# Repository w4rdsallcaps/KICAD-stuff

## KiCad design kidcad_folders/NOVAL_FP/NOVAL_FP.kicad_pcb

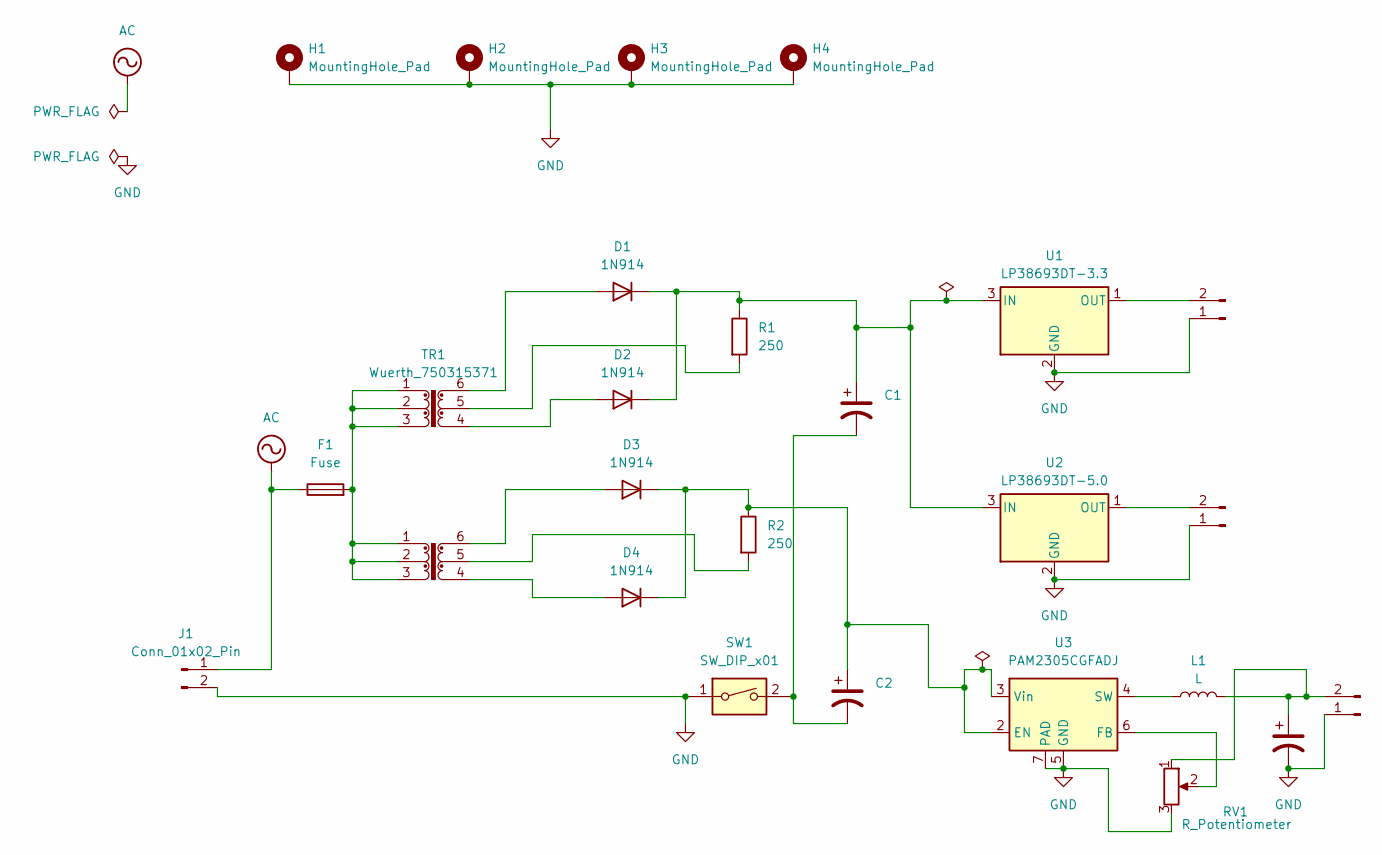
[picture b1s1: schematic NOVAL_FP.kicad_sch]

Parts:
C1, C2, C3: C_Polarized_US; CP_Axial_L10.0mm_D4.5mm_P15.00mm_Horizontal
D1, D2, D3, D4: 1N914; D_DO-35_SOD27_P7.62mm_Horizontal
F1: Fuse; L_TechFuse_SL0420
H1, H2, H3, H4: MountingHole_Pad; MountingHole_2.2mm_M2_DIN965_Pad
J1, J2, J3, J4: Conn_01x02_Pin; PhoenixContact_MSTBA_2,5_2-G-5,08_1x02_P5.08mm_Horizontal
L1: L; L_Wurth_WE-LQSH-2010
R1, R2: 250; R_Axial_DIN0204_L3.6mm_D1.6mm_P7.62mm_Horizontal
RV1: R_Potentiometer; Potentiometer_Bourns_3266Y_Vertical
SW1: SW_DIP_x01; SW_DIP_SPSTx01_Slide_6.7x4.1mm_W8.61mm_P2.54mm_LowProfile
TR1, TR2: Wuerth_750315371; Transformer_Wuerth_750315371
U1: LP38693DT-3.3; TO-252-2
U2: LP38693DT-5.0; TO-252-2
U3: PAM2305CGFADJ; DFN-6-1EP_2x2mm_P0.65mm_EP1x1.6mm

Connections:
AC: F1.1, J1.1
GND: C3.2, H1.1 (1_1), H2.1 (1_1), H3.1 (1_1), H4.1 (1_1), J1.2, J2.1, J3.1, J4.1, RV1.3, SW1.1, U1.2 (GND), U2.2 (GND), U3.5 (GND), U3.7 (PAD)
unnamed: C1.2, C2.2, SW1.2
unnamed: D1.2 (A), TR1.6
unnamed: C1.1, D1.1 (K), D2.1 (K), R1.1, U1.3 (IN), U2.3 (IN)
unnamed: D2.2 (A), TR1.4
unnamed: D3.2 (A), TR2.6
unnamed: C2.1, D3.1 (K), D4.1 (K), R2.1, U3.2 (EN), U3.3 (Vin)
unnamed: D4.2 (A), TR2.4
unnamed: F1.2, TR1.1, TR1.2, TR1.3, TR2.1, TR2.2, TR2.3
unnamed: C3.1, J2.2, L1.2, RV1.1
unnamed: J3.2, U2.1 (OUT)
unnamed: J4.2, U1.1 (OUT)
unnamed: R1.2, TR1.5
unnamed: R2.2, TR2.5
unnamed: RV1.2, U3.6 (FB)
unnamed: L1.1, U3.4 (SW)

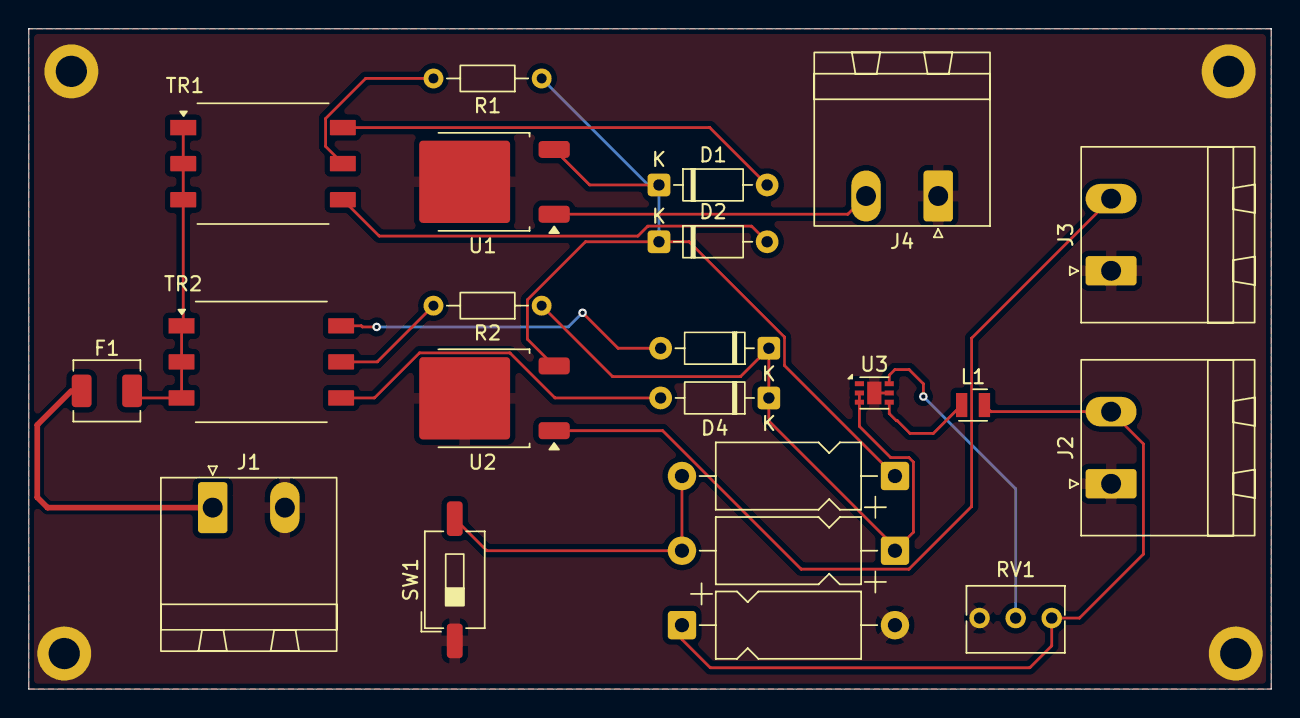
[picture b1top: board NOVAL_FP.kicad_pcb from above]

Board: 2 copper layers, 87.5 x 46.5 mm, 26 parts (0 on the bottom side), 17 nets.

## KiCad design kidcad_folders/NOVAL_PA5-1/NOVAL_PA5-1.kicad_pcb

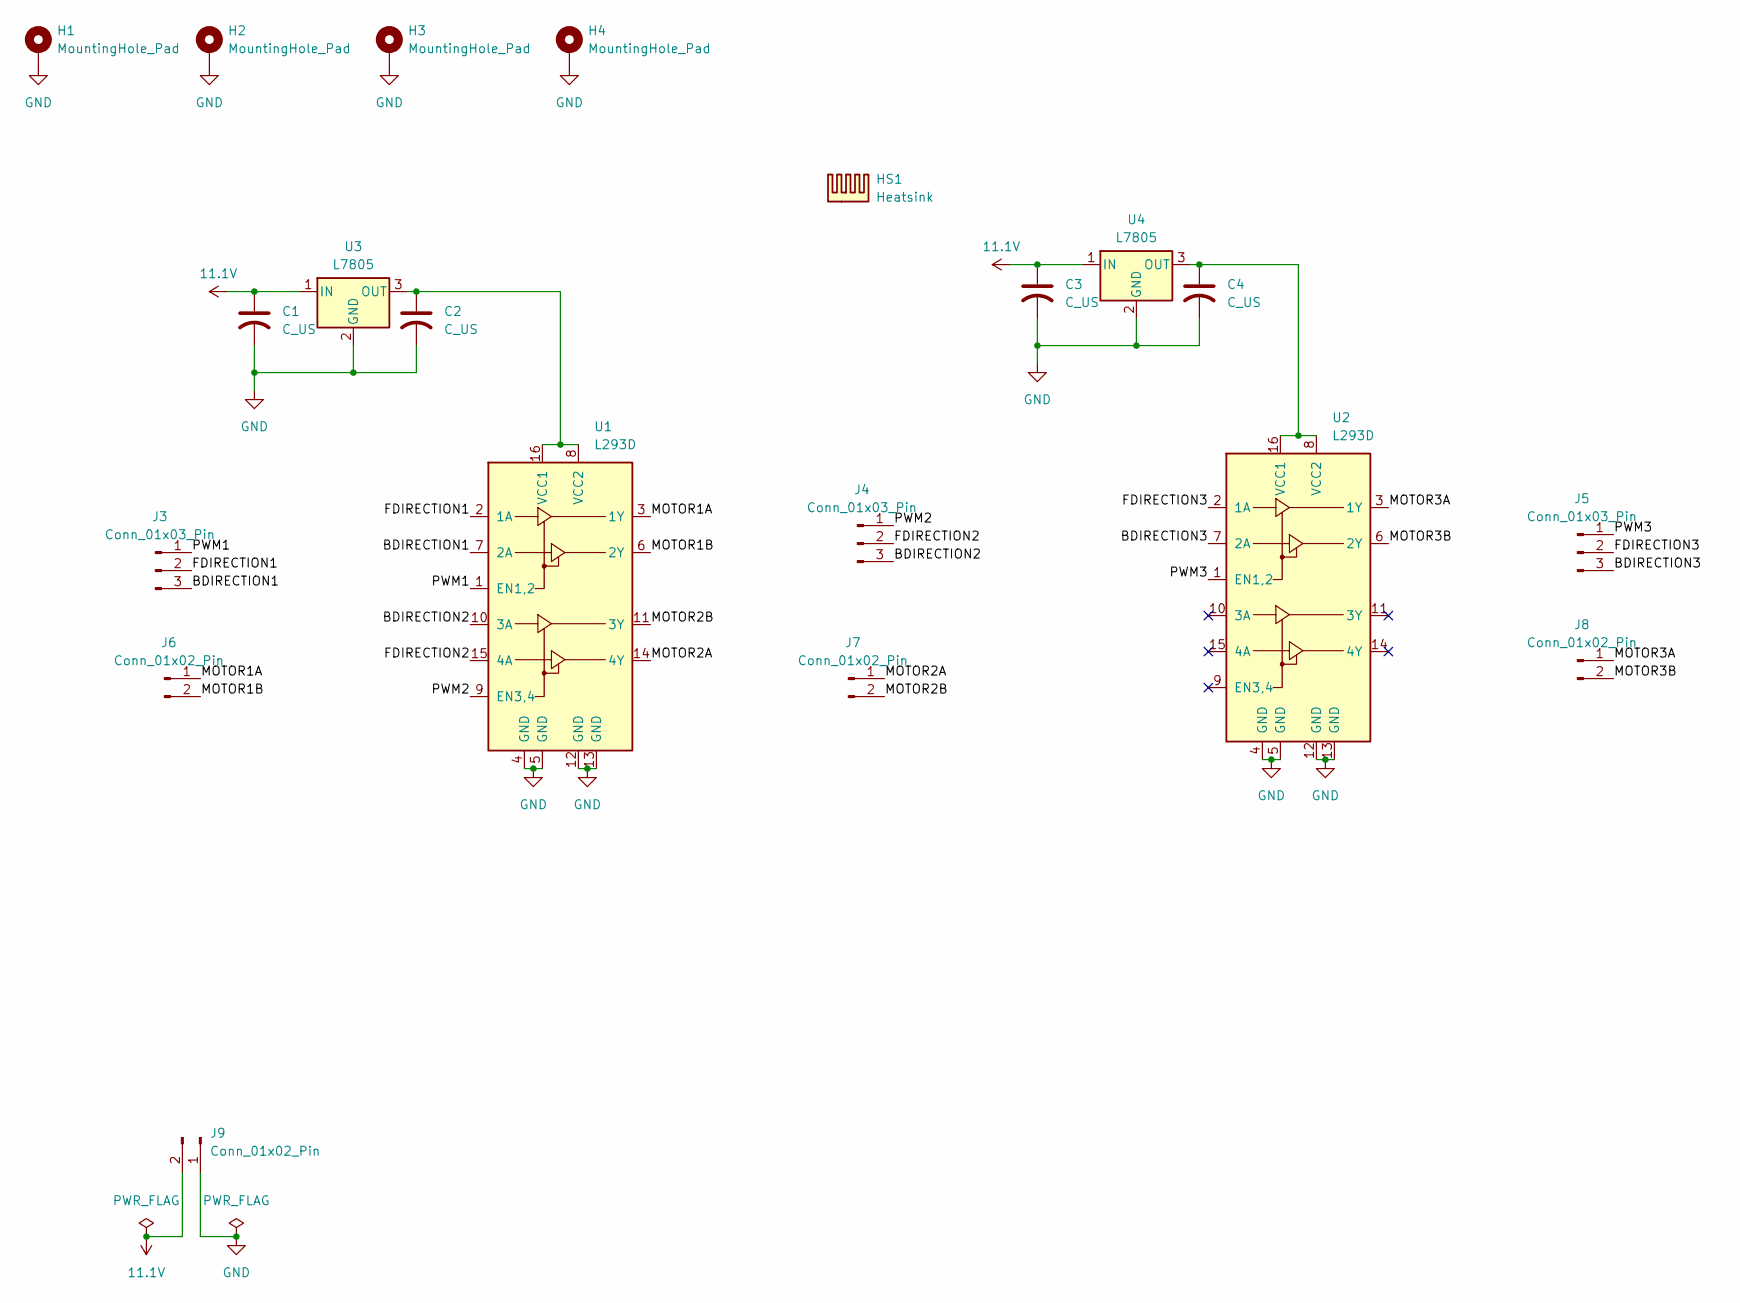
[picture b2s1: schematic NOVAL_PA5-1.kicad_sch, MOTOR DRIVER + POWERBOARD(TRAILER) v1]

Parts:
C1, C2, C3, C4: C_US; C_Axial_L5.1mm_D3.1mm_P10.00mm_Horizontal
H1, H2, H3, H4: MountingHole_Pad; MountingHole_2.2mm_M2_DIN965_Pad
HS1: Heatsink
J3, J4, J5: Conn_01x03_Pin; JST_PH_S3B-PH-K_1x03_P2.00mm_Horizontal
J6, J7, J8, J9: Conn_01x02_Pin; JST_EH_S2B-EH_1x02_P2.50mm_Horizontal
U1, U2: L293D; DIP-16_W7.62mm
U3, U4: L7805; TO-220-3_Vertical

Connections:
11.1V: C1.1, C3.1, J9.2, U3.1 (IN), U4.1 (IN)
/BDIRECTION1: J3.3, U1.7 (2A)
/BDIRECTION2: J4.3, U1.10 (3A)
/BDIRECTION3: J5.3, U2.7 (2A)
/FDIRECTION1: J3.2, U1.2 (1A)
/FDIRECTION2: J4.2, U1.15 (4A)
/FDIRECTION3: J5.2, U2.2 (1A)
/MOTOR1A: J6.1, U1.3 (1Y)
/MOTOR1B: J6.2, U1.6 (2Y)
/MOTOR2A: J7.1, U1.14 (4Y)
/MOTOR2B: J7.2, U1.11 (3Y)
/MOTOR3A: J8.1, U2.3 (1Y)
/MOTOR3B: J8.2, U2.6 (2Y)
/PWM1: J3.1, U1.1 (EN1,2)
/PWM2: J4.1, U1.9 (EN3,4)
/PWM3: J5.1, U2.1 (EN1,2)
GND: C1.2, C2.2, C3.2, C4.2, H1.1 (1_1), H2.1 (1_1), H3.1 (1_1), H4.1 (1_1), J9.1, U1.4 (GND), U1.5 (GND), U1.12 (GND), U1.13 (GND), U2.4 (GND), U2.5 (GND), U2.12 (GND), U2.13 (GND), U3.2 (GND), U4.2 (GND)
unnamed: C2.1, U1.8 (VCC2), U1.16 (VCC1), U3.3 (OUT)
unnamed: C4.1, U2.8 (VCC2), U2.16 (VCC1), U4.3 (OUT)

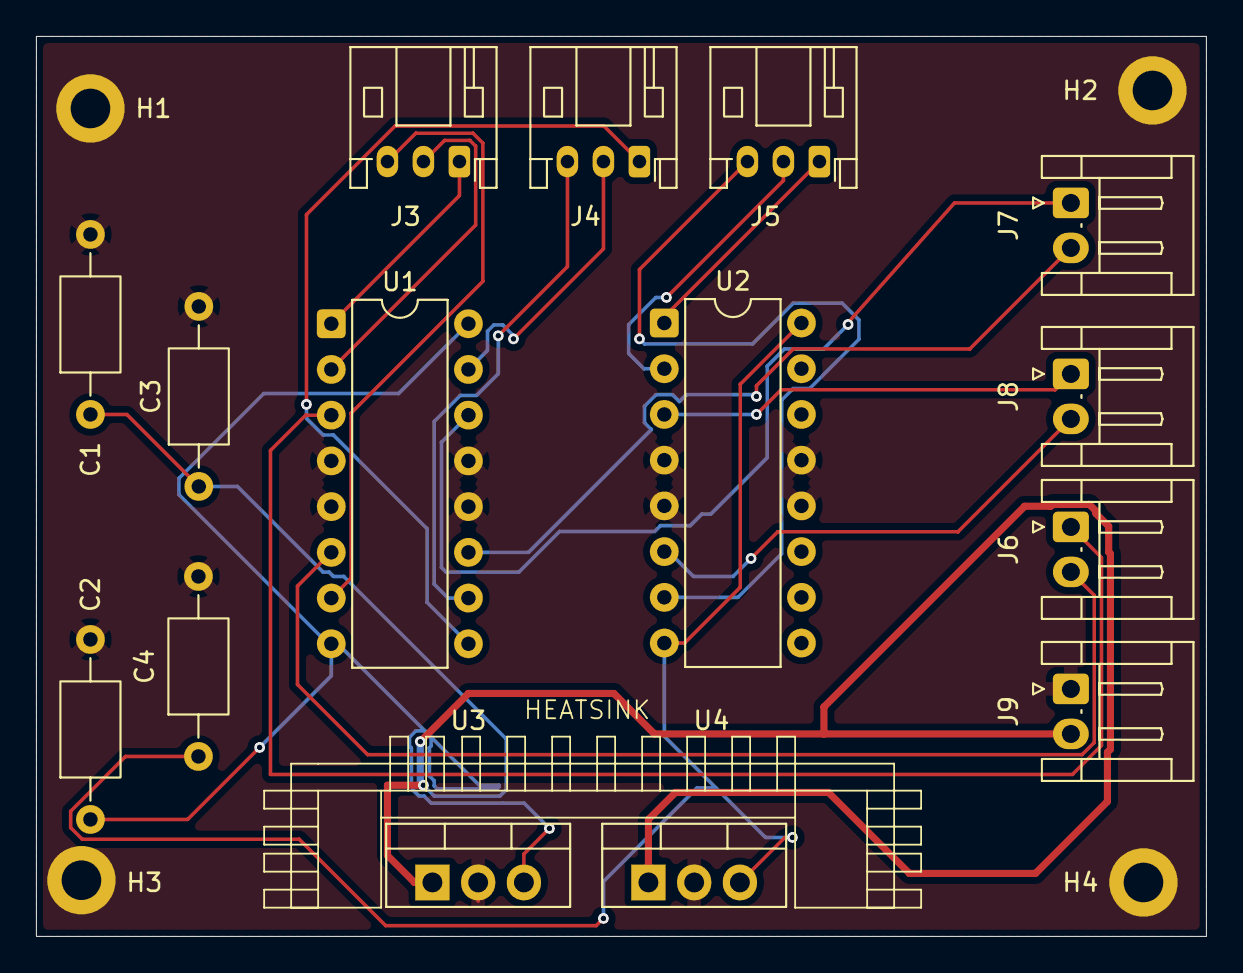
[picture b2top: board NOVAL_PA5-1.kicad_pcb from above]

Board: 2 copper layers, 65.0 x 50.0 mm, 19 parts (0 on the bottom side), 19 nets.

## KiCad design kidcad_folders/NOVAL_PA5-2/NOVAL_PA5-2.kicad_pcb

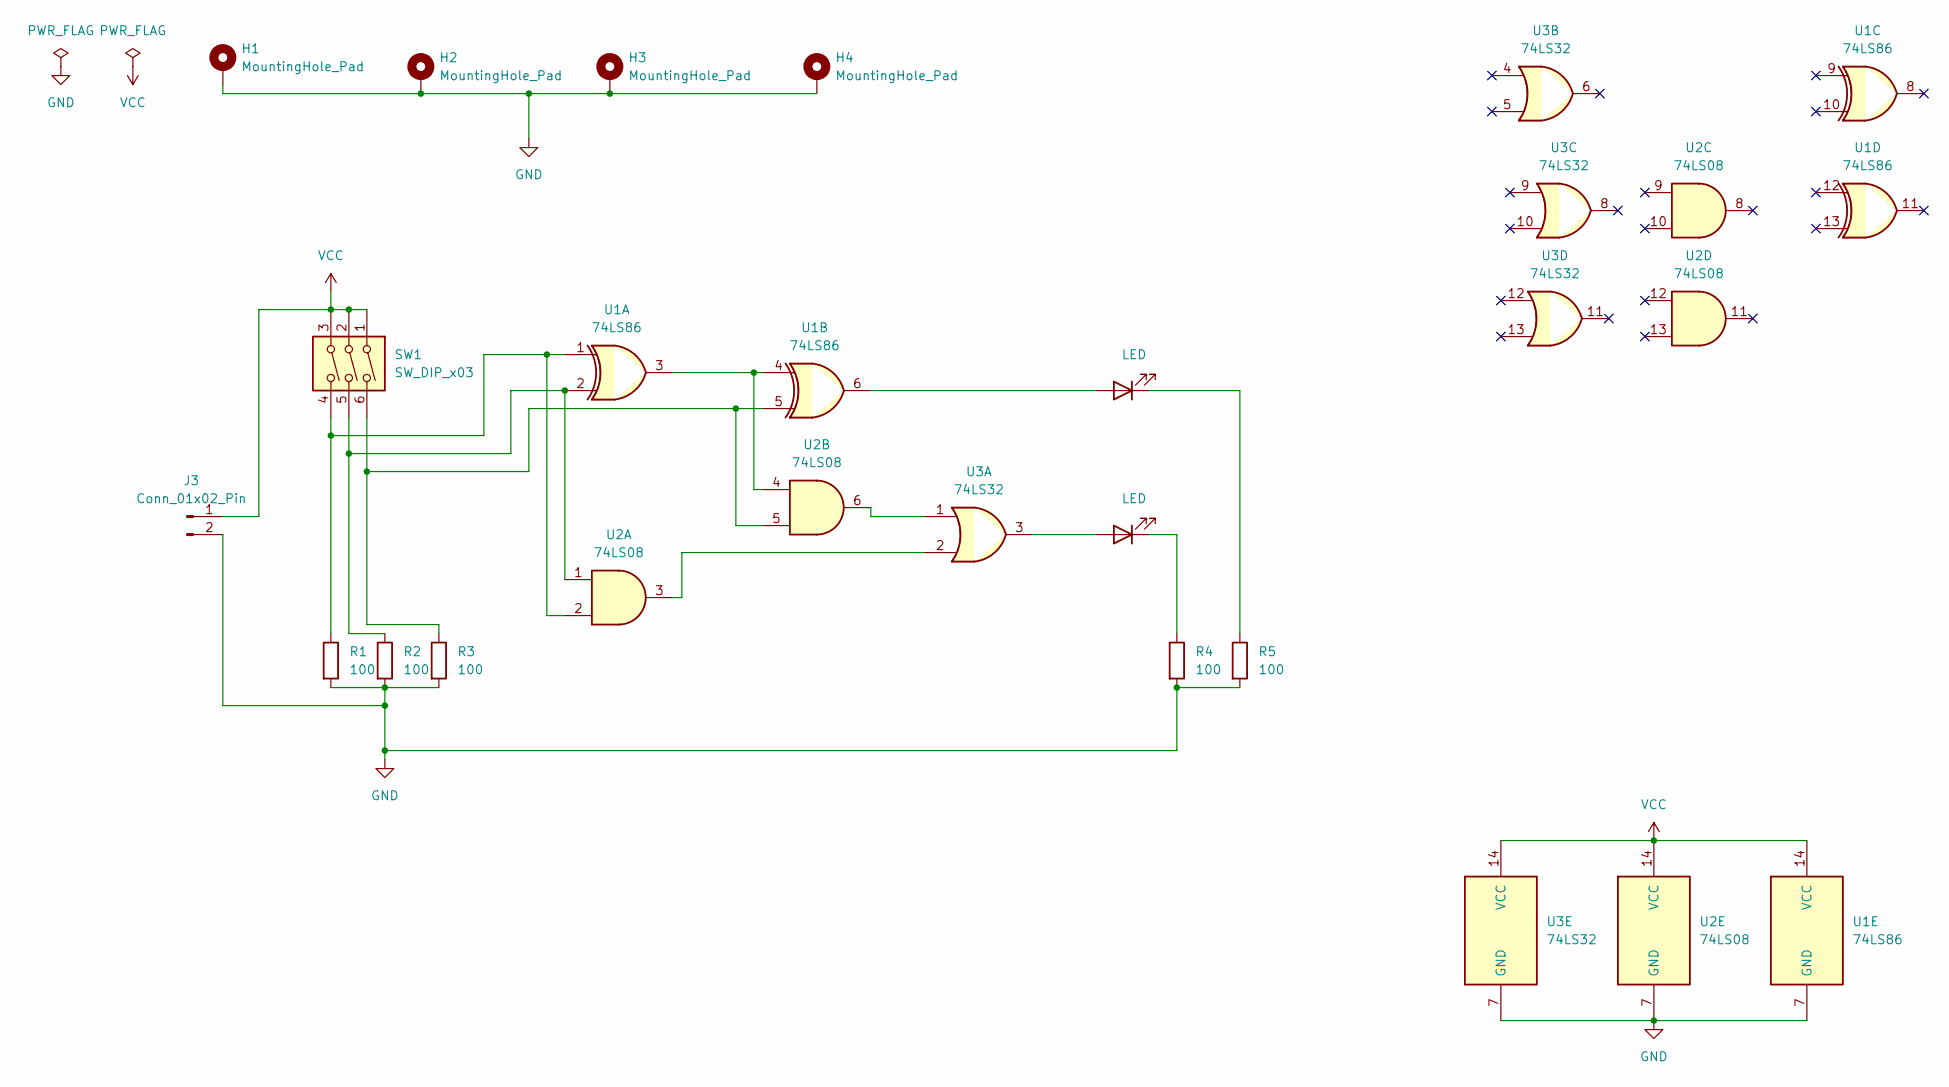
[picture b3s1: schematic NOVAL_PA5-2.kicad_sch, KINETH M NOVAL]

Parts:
H1, H2, H3, H4: MountingHole_Pad; MountingHole_2.2mm_M2_DIN965_Pad
J3: Conn_01x02_Pin; PinHeader_1x02_P2.00mm_Horizontal
L1, L2: LED; LED_D3.0mm
R1, R2, R3, R4, R5: 100; R_Axial_DIN0204_L3.6mm_D1.6mm_P5.08mm_Horizontal
SW1: SW_DIP_x03; MS12ANG03
U1: 74LS86; DIP-14_W7.62mm
U2: 74LS08; DIP-14_W7.62mm
U3: 74LS32; DIP-14_W7.62mm

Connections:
GND: H1.1 (1_1), H2.1 (1_1), H3.1 (1_1), H4.1 (1_1), J3.2, R1.2, R2.2, R3.2, R4.2, R5.2, U1.7 (GND), U2.7 (GND), U3.7 (GND)
unnamed: L1.2 (A), U1.6
unnamed: L1.1 (K), R5.1
unnamed: L2.2 (A), U3.3
unnamed: L2.1 (K), R4.1
unnamed: R1.1, SW1.4, U1.1, U2.2
unnamed: R2.1, SW1.5, U1.2, U2.1
unnamed: R3.1, SW1.6, U1.5, U2.5
unnamed: U1.3, U1.4, U2.4
unnamed: U2.3, U3.2
unnamed: U2.6, U3.1
VCC: J3.1, SW1.1, SW1.2, SW1.3, U1.14 (VCC), U2.14 (VCC), U3.14 (VCC)

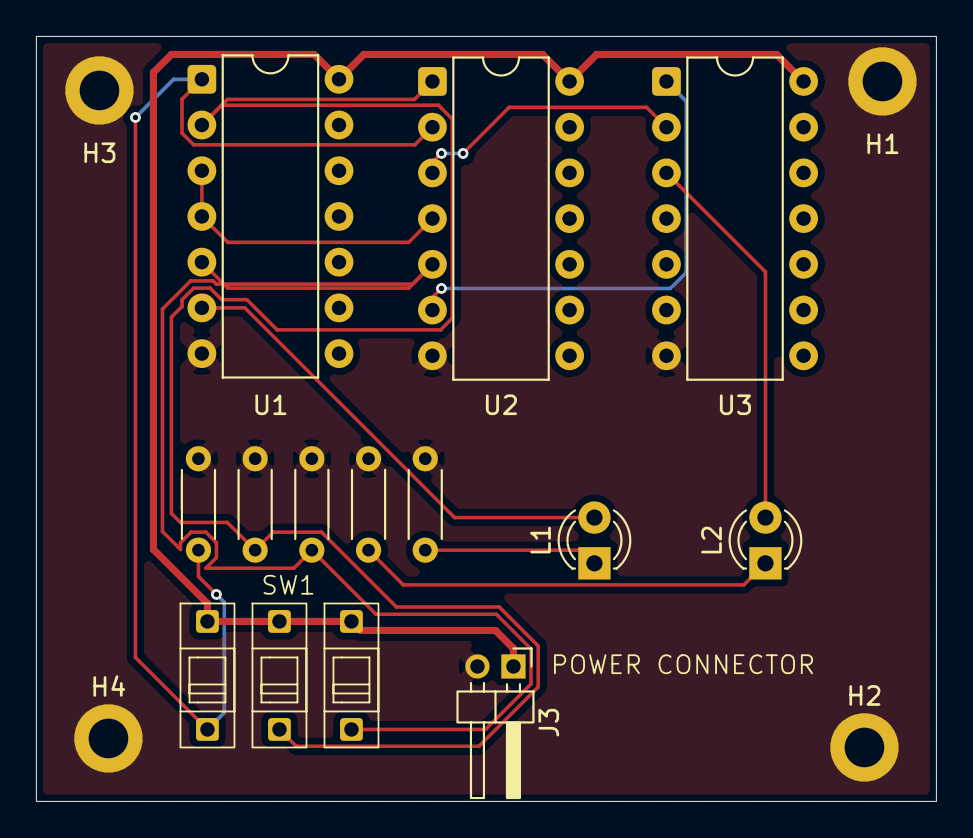
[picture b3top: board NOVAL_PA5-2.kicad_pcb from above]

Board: 2 copper layers, 50.0 x 42.5 mm, 16 parts (0 on the bottom side), 12 nets.

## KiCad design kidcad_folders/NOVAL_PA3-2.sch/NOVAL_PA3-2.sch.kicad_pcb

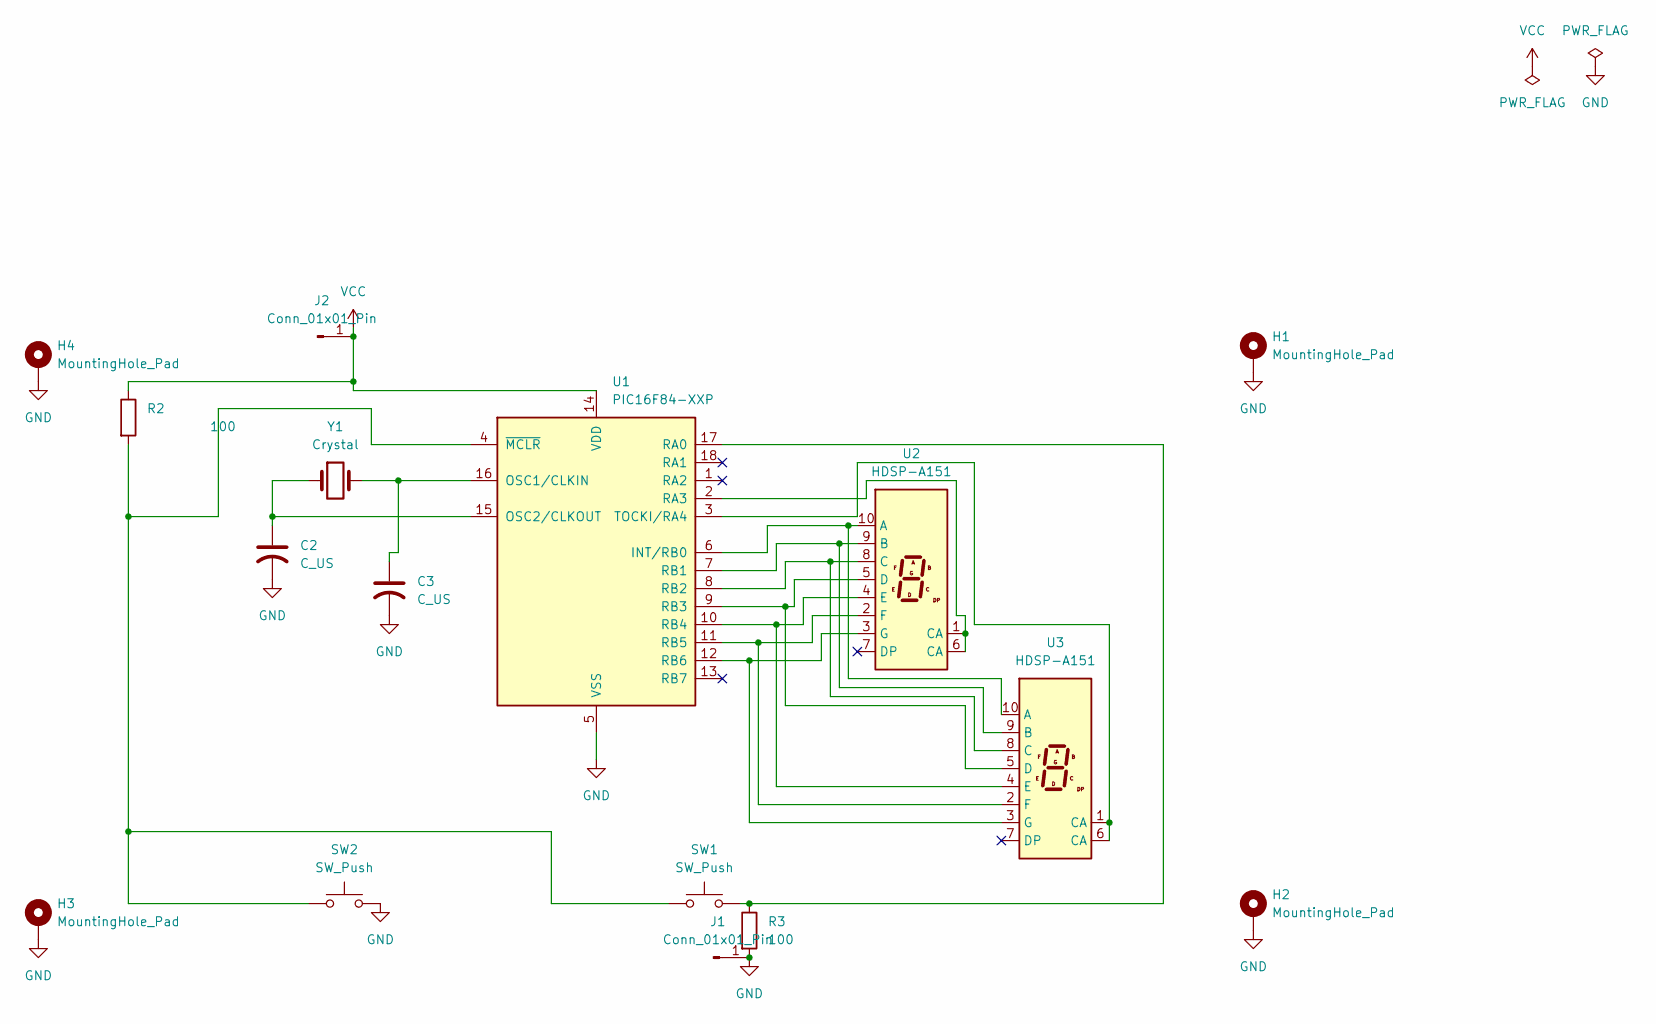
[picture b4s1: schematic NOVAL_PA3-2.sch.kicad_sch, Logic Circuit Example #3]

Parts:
C2, C3: C_US; CP_Axial_L10.0mm_D4.5mm_P15.00mm_Horizontal
H1, H2, H3, H4: MountingHole_Pad; MountingHole_3mm_Pad
J1, J2: Conn_01x01_Pin; SolderWire-0.127sqmm_1x01_D0.48mm_OD1mm
R2, R3: 100; R_Axial_DIN0204_L3.6mm_D1.6mm_P5.08mm_Horizontal
SW1, SW2: SW_Push; SW_PUSH_1P1T_6x3.5mm_H5.0_APEM_MJTP1250
U1: PIC16F84-XXP; DIP-18_W7.62mm
U2, U3: HDSP-A151
Y1: Crystal; Crystal_C38-LF_D3.0mm_L8.0mm_Vertical

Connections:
GND: C2.2, C3.2, H1.1 (1_1), H2.1 (1_1), H3.1 (1_1), H4.1 (1_1), J1.1 (Pin_1_1), R3.2, SW2.2, U1.5 (VSS)
unnamed: U1.6 (INT/RB0), U2.10 (A), U3.10 (A)
unnamed: C3.1, U1.16 (OSC1/CLKIN), Y1.2
unnamed: C2.1, U1.15 (OSC2/CLKOUT), Y1.1
unnamed: R3.1, SW1.2, U1.17 (RA0)
unnamed: U1.2 (RA3), U2.1 (CA), U2.6 (CA)
unnamed: U1.7 (RB1), U2.9 (B), U3.9 (B)
unnamed: U1.8 (RB2), U2.8 (C), U3.8 (C)
unnamed: U1.9 (RB3), U2.5 (D), U3.5 (D)
unnamed: U1.10 (RB4), U2.4 (E), U3.4 (E)
unnamed: U1.11 (RB5), U2.2 (F), U3.2 (F)
unnamed: U1.12 (RB6), U2.3 (G), U3.3 (G)
unnamed: U1.3 (TOCKI/RA4), U3.1 (CA), U3.6 (CA)
unnamed: R2.2, SW1.1, SW2.1, U1.4 (~MCLR)
VCC: J2.1 (Pin_1_1), R2.1, U1.14 (VDD)

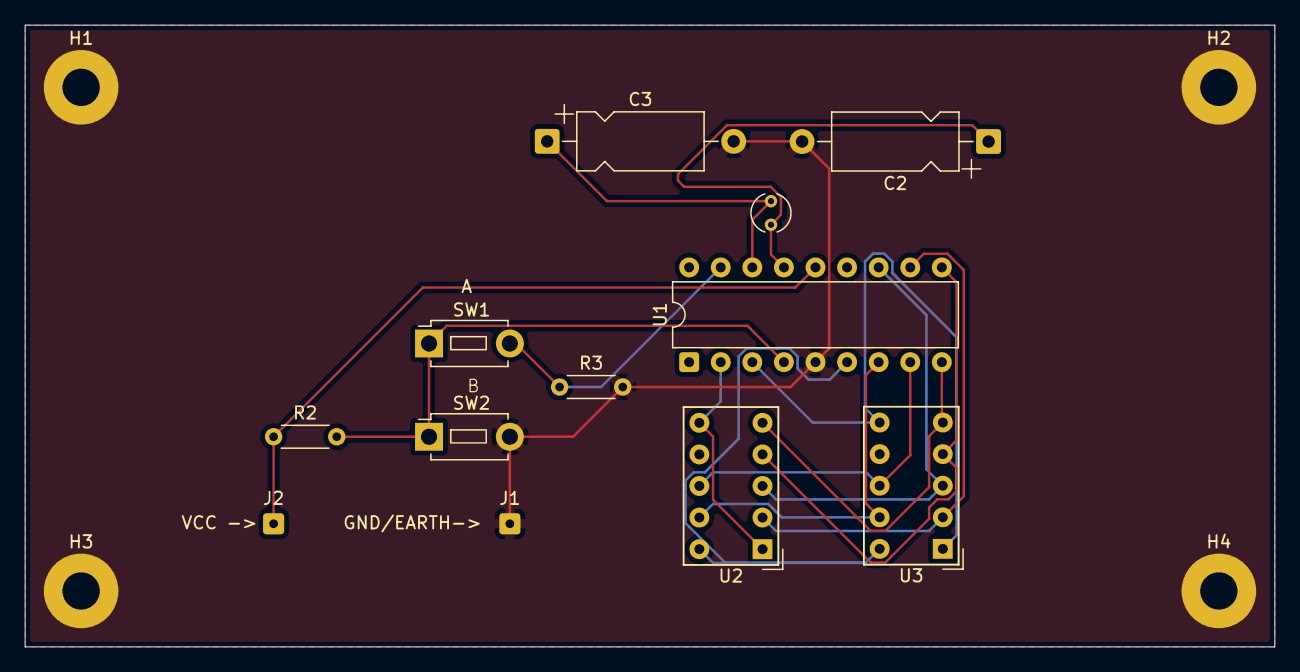
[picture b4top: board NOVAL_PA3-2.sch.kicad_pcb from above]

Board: 2 copper layers, 100.5 x 50.0 mm, 16 parts (0 on the bottom side), 15 nets.

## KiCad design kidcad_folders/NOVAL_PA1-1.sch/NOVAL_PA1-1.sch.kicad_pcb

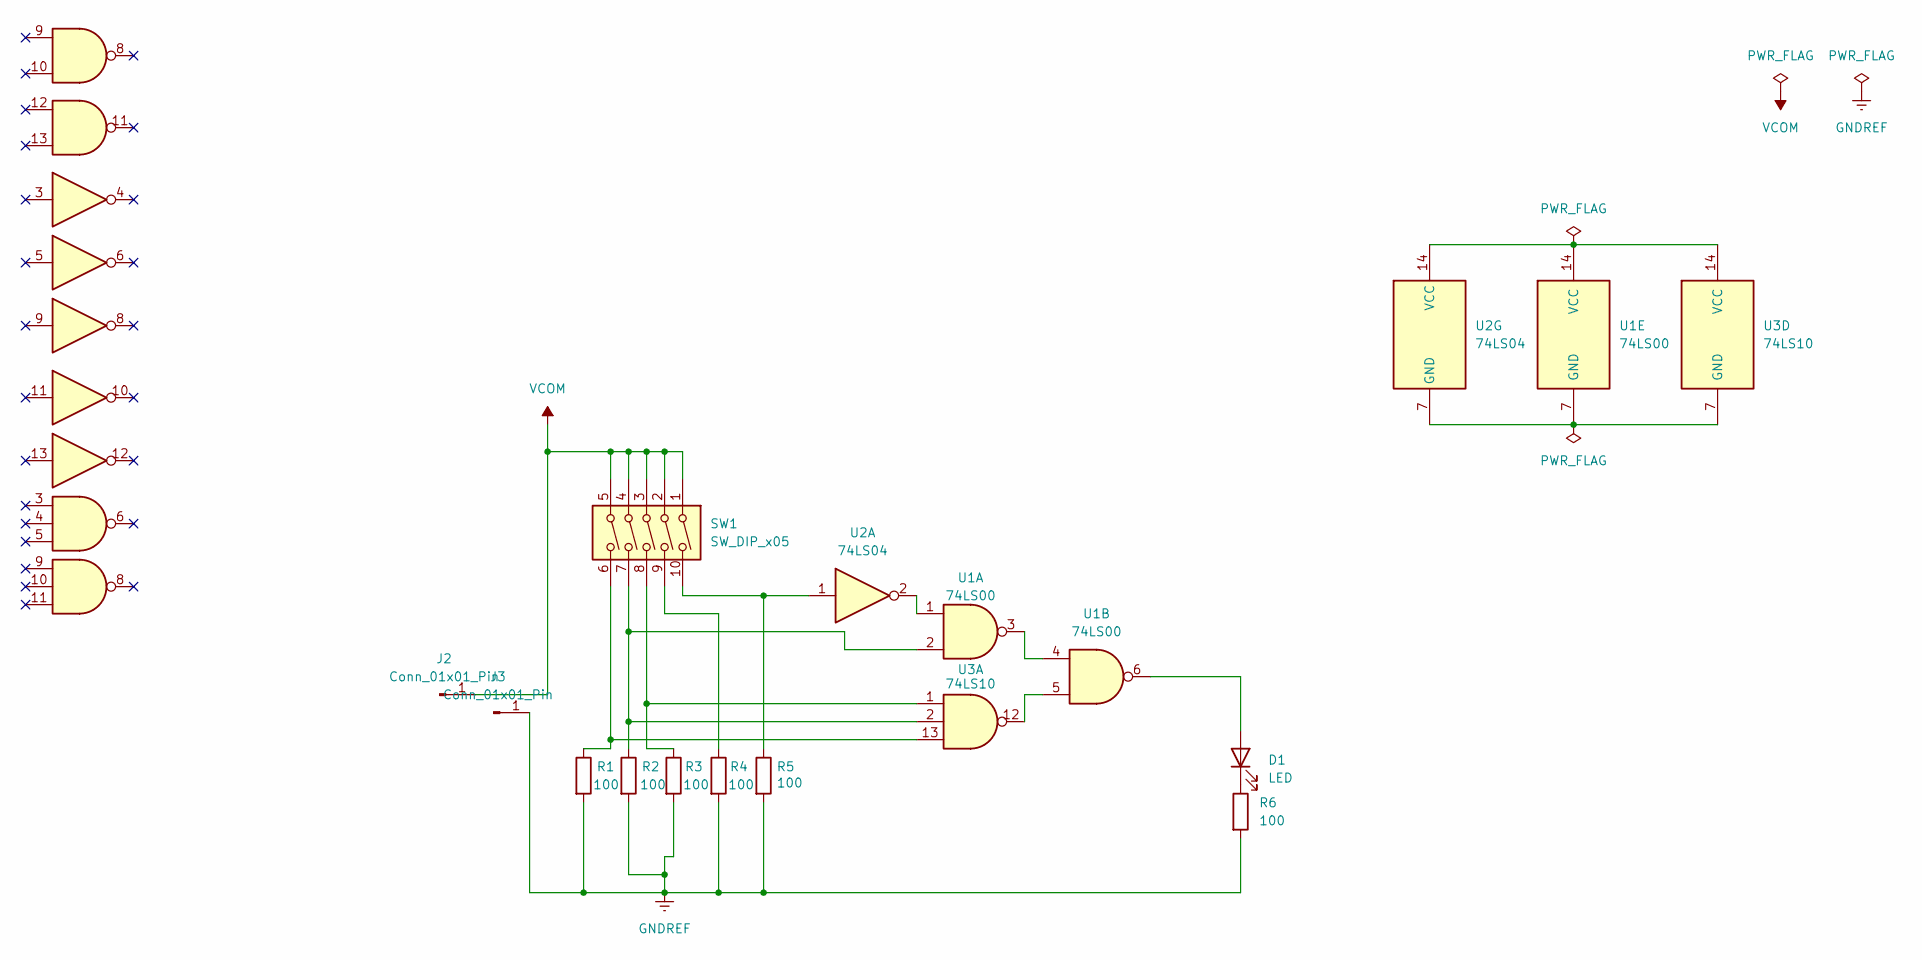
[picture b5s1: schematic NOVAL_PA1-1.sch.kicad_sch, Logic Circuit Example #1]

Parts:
D1: LED; LED_D3.0mm_Clear
J2, J3: Conn_01x01_Pin; SolderWire-1.5sqmm_1x01_D1.7mm_OD3.9mm
R1, R2, R3, R4, R5, R6: 100; R_Axial_DIN0207_L6.3mm_D2.5mm_P7.62mm_Horizontal
SW1: SW_DIP_x05; SW_DIP_SPSTx05_Slide_9.78x14.88mm_W7.62mm_P2.54mm
U1: 74LS00; DIP-14_W10.16mm
U2: 74LS04; DIP-14_W10.16mm
U3: 74LS10; DIP-14_W10.16mm

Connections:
GNDREF: J3.1 (Pin_1_1), R1.2, R2.2, R3.2, R4.2, R5.2, R6.2
unnamed: D1.2 (A), U1.6
unnamed: D1.1 (K), R6.1
unnamed: R1.1, SW1.6, U3.13
unnamed: R2.1, SW1.7, U1.2, U3.2
unnamed: R3.1, SW1.8, U3.1
unnamed: R4.1, SW1.9
unnamed: R5.1, SW1.10, U2.1
unnamed: U1.1, U2.2
unnamed: U1.3, U1.4
unnamed: U1.5, U3.12
unnamed: U1.7 (GND), U2.7 (GND), U3.7 (GND)
unnamed: U1.14 (VCC), U2.14 (VCC), U3.14 (VCC)
VCOM: J2.1 (Pin_1_1), SW1.1, SW1.2, SW1.3, SW1.4, SW1.5

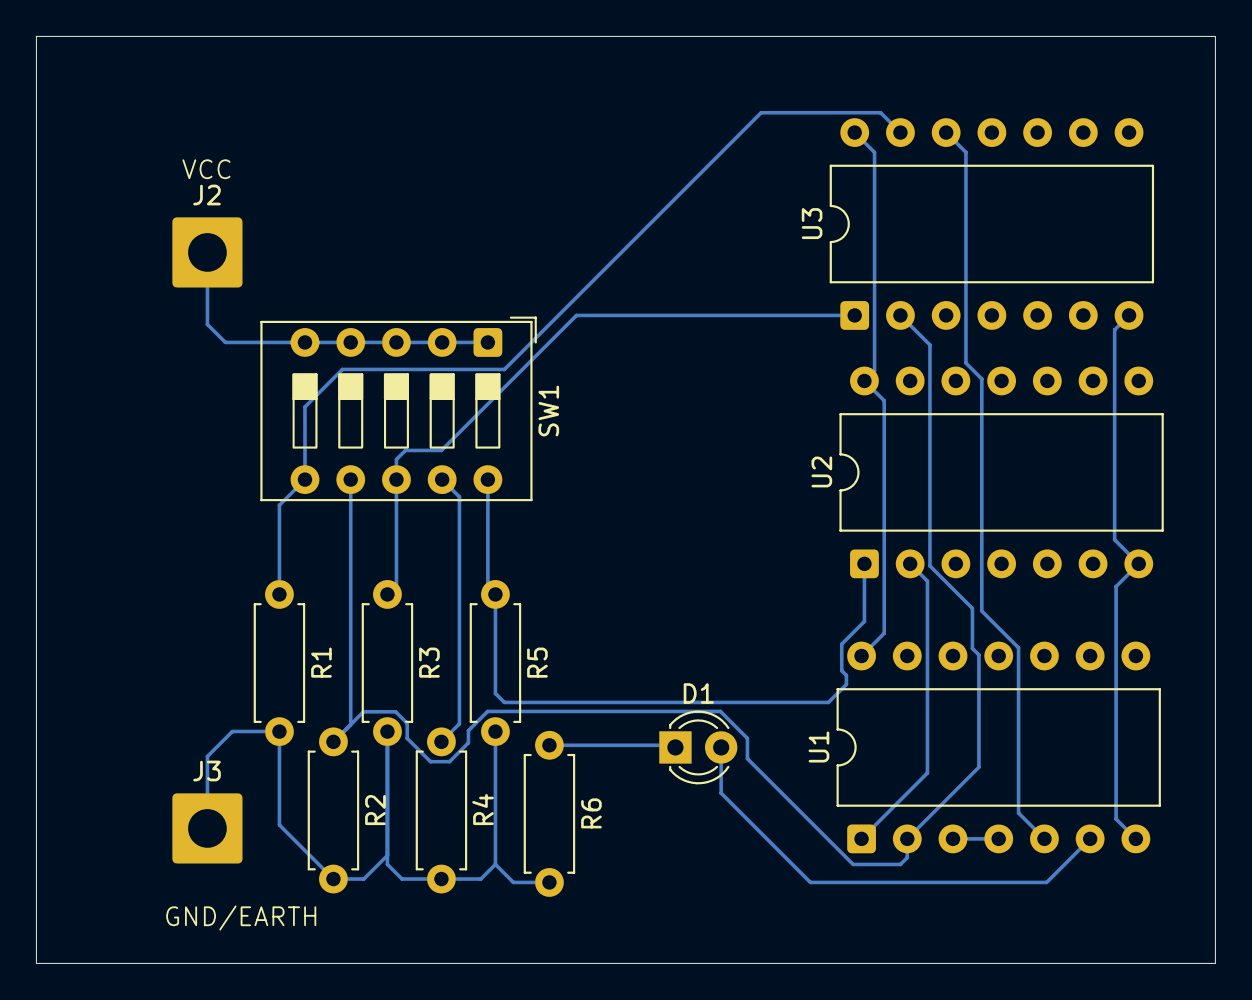
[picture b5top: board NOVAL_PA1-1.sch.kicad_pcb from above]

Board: 2 copper layers, 65.5 x 51.5 mm, 13 parts (0 on the bottom side), 14 nets.

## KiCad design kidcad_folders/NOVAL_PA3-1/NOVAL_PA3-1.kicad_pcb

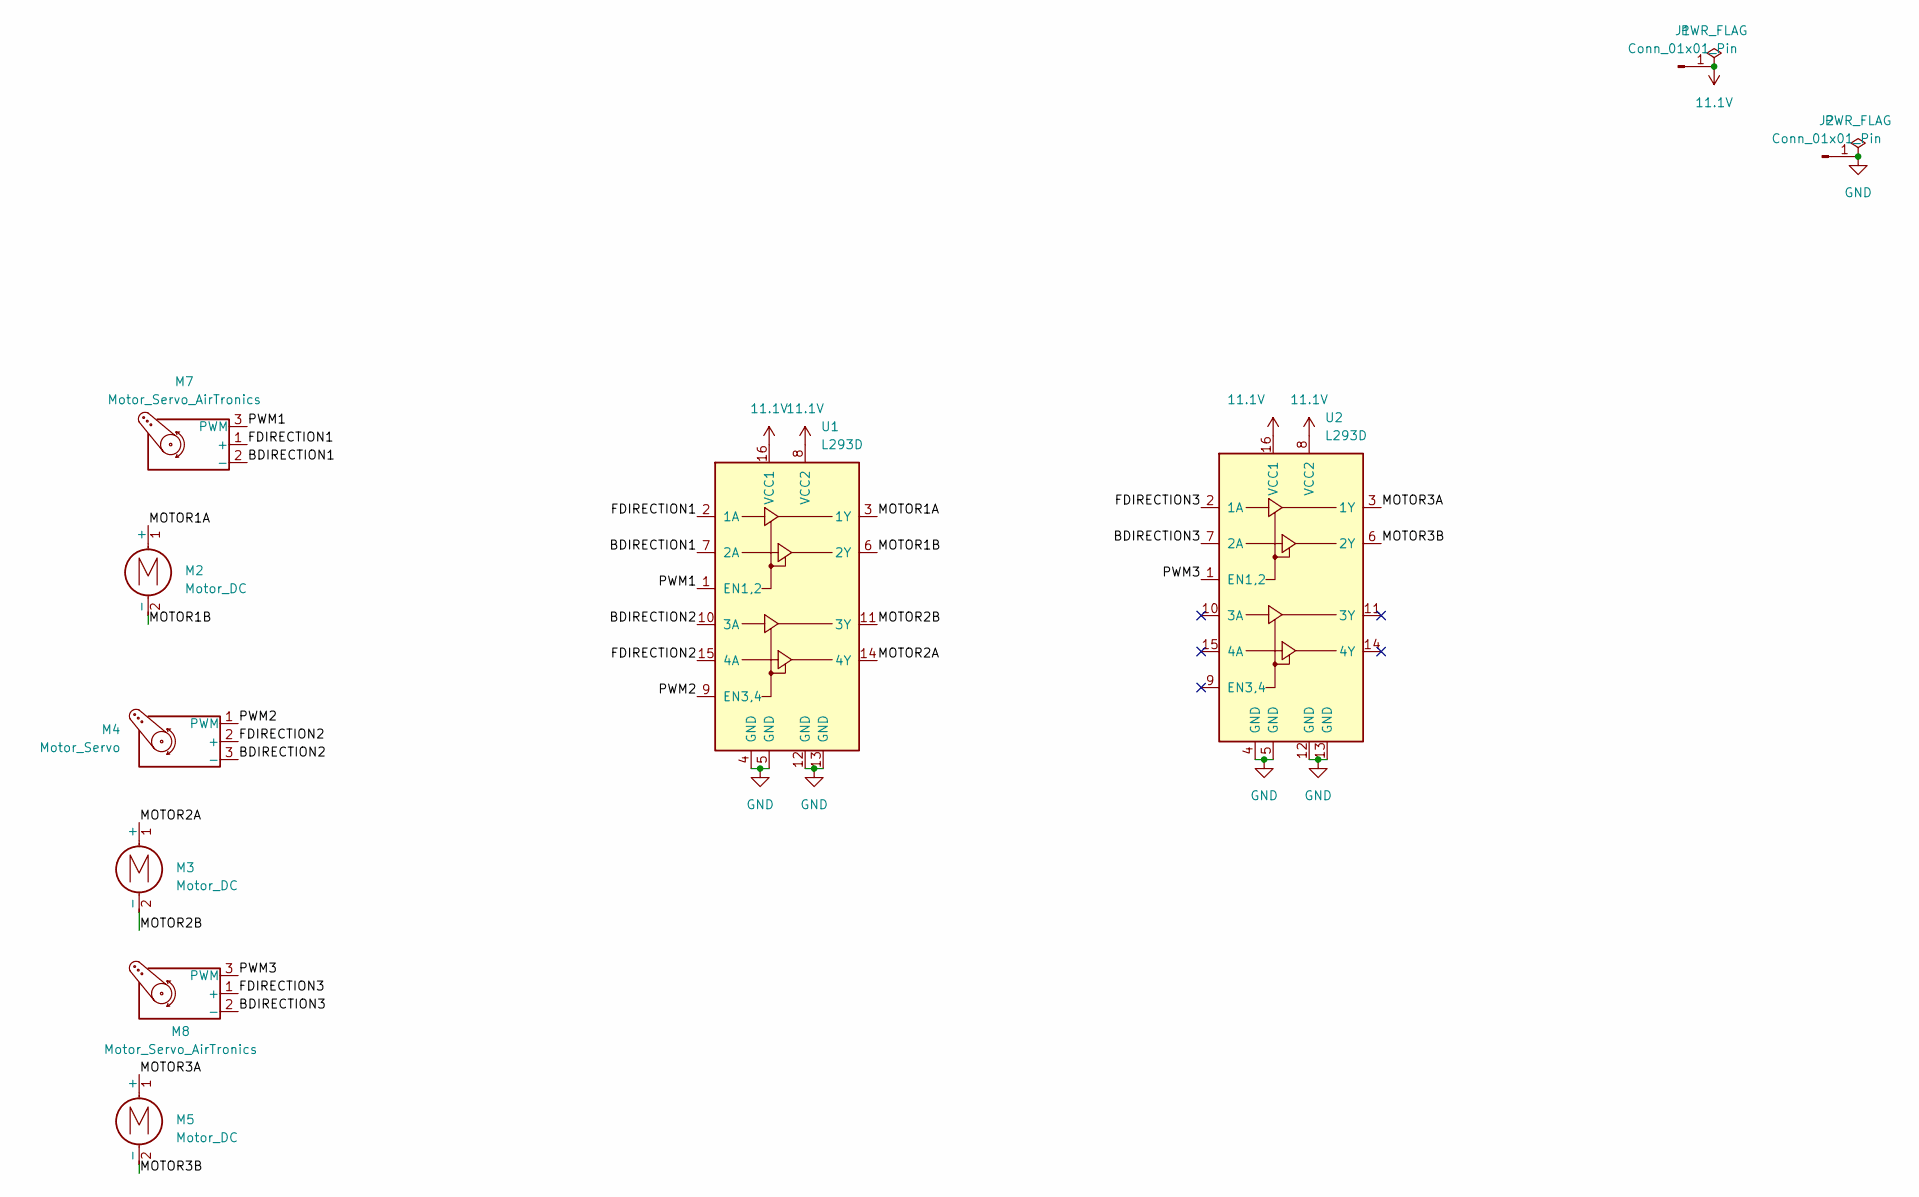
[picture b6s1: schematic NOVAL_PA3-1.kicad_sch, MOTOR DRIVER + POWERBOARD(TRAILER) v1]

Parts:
J1, J2: Conn_01x01_Pin; SolderWire-0.75sqmm_1x01_D1.25mm_OD2.3mm
M2, M3, M5: Motor_DC; PinHeader_1x02_P2.54mm_Vertical
M4: Motor_Servo; PinHeader_1x03_P2.54mm_Vertical
M7, M8: Motor_Servo_AirTronics; PinHeader_1x03_P2.54mm_Vertical
U1, U2: L293D; DIP-16_W7.62mm

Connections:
11.1V: J1.1 (Pin_1_1), U1.8 (VCC2), U1.16 (VCC1), U2.8 (VCC2), U2.16 (VCC1)
/BDIRECTION1: M7.2 (-), U1.7 (2A)
/BDIRECTION2: M4.3 (-), U1.10 (3A)
/BDIRECTION3: M8.2 (-), U2.7 (2A)
/FDIRECTION1: M7.1 (+), U1.2 (1A)
/FDIRECTION2: M4.2 (+), U1.15 (4A)
/FDIRECTION3: M8.1 (+), U2.2 (1A)
/MOTOR1A: M2.1 (+), U1.3 (1Y)
/MOTOR1B: M2.2 (-), U1.6 (2Y)
/MOTOR2A: M3.1 (+), U1.14 (4Y)
/MOTOR2B: M3.2 (-), U1.11 (3Y)
/MOTOR3A: M5.1 (+), U2.3 (1Y)
/MOTOR3B: M5.2 (-), U2.6 (2Y)
/PWM1: M7.3 (PWM), U1.1 (EN1,2)
/PWM2: M4.1 (PWM), U1.9 (EN3,4)
/PWM3: M8.3 (PWM), U2.1 (EN1,2)
GND: J2.1 (Pin_1_1), U1.4 (GND), U1.5 (GND), U1.12 (GND), U1.13 (GND), U2.4 (GND), U2.5 (GND), U2.12 (GND), U2.13 (GND)

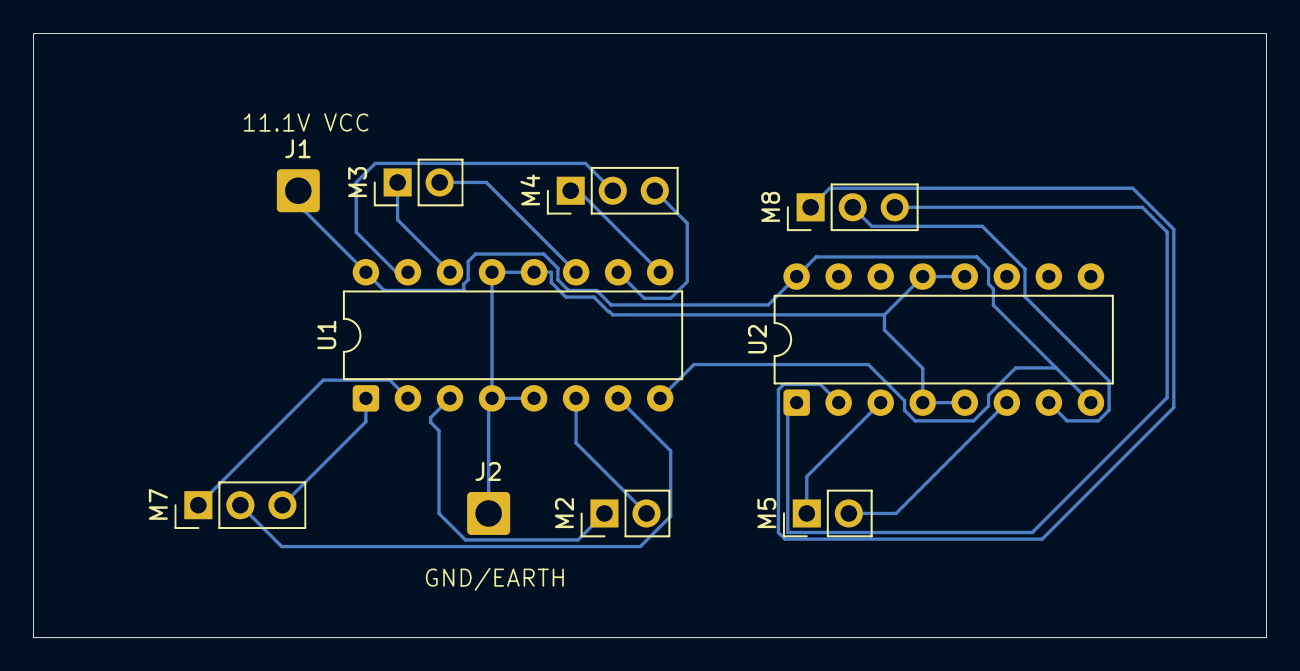
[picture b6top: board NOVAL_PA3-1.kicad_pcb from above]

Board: 2 copper layers, 74.5 x 36.5 mm, 10 parts (0 on the bottom side), 17 nets.
